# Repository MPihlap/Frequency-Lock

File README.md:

# Frequency-Lock

## Demonstration video:
https://www.youtube.com/watch?v=SHbAAHV13OE

## Overview
Result of a hardware project done for a course at University of Tartu. It is a custom board design built around the STM32F4 microcontroller. 
The system records audio in 0.2 second buffers, performs RFFT and analyzes the output to see if the correct note is being played.

The code is fully compatible with the STM32F4 Discovery board.

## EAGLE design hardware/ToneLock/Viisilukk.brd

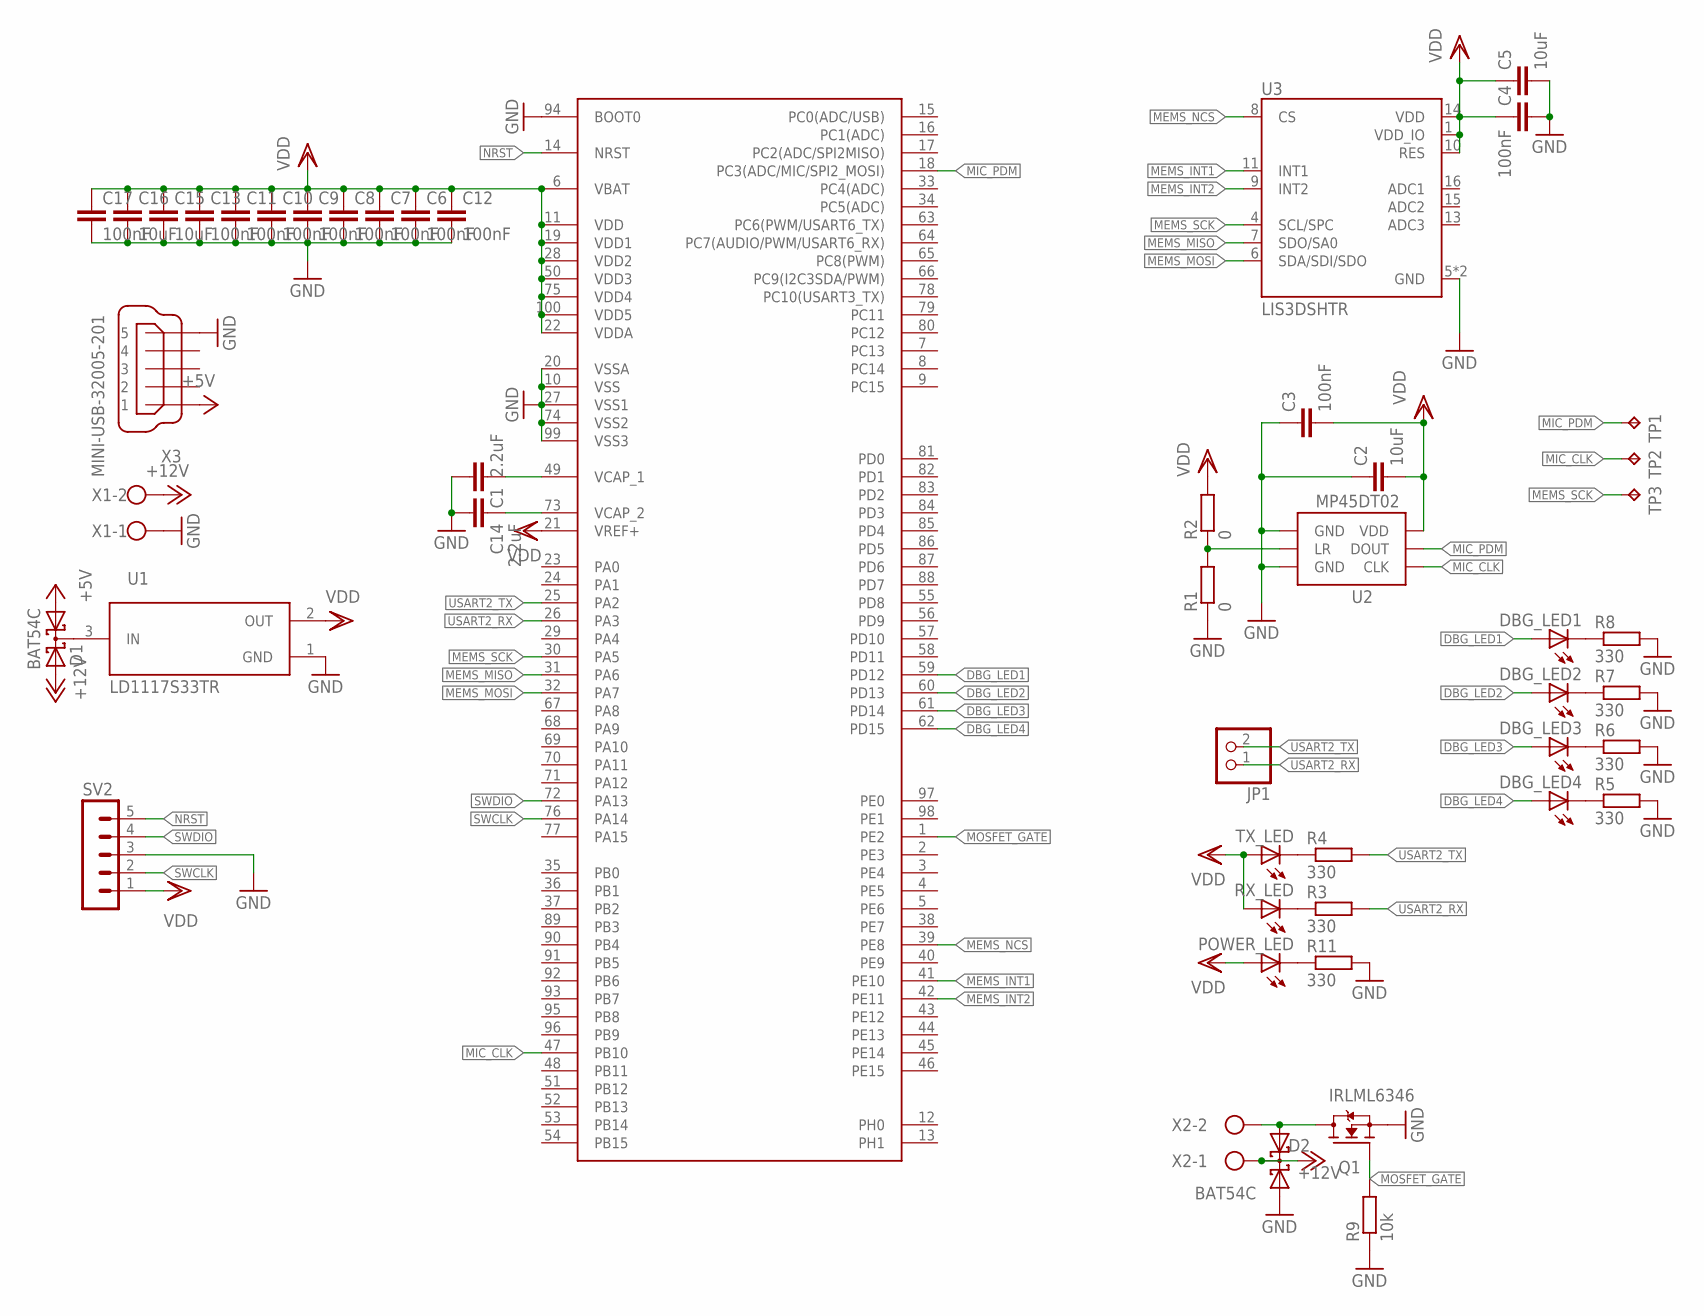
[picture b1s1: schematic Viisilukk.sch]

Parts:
C1, C14: 2.2uF; C0603
C2, C5, C15, C16: 10uF; C0805
C3, C4, C6, C7, C8, C9, C10, C11, C12, C13, C17: 100nF; C0603
D1, D2: BAT54C; SOT23
DBG_LED1, DBG_LED2, DBG_LED3, DBG_LED4: LEDCHIP-LED0603; CHIP-LED0603
JP1: PINHD-1X2; 1X02
POWER_LED: LEDCHIP-LED0603; CHIP-LED0603
Q1: IRLML6346; SOT23
R1, R2: 0; R0603
R3, R4, R5, R6, R7, R8, R11: 330; R0603
R9: 10k; R0603
RX_LED: LEDCHIP-LED0603; CHIP-LED0603
SV2: MA05-1
TP1, TP2, TP3: TPB2,54; B2,54
TX_LED: LEDCHIP-LED0603; CHIP-LED0603
U1: LD1117S33TR; SOT230P700X180-4N
U2: MP45DT02; ST_HLGA6
U3: LIS3DSHTR; LGA16R50P5X3_300X300X100N
U$1: STM32F407STM32D40X; LQFP100
X1, X2: W237-102
X3: MINI-USB-32005-201; 32005-201

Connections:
+5V: D1.1 (A1), X3.1
+12V: D1.2 (A2), D2.3 (CC), X1.2, X2.1
DBG_LED1: DBG_LED1.A, U$1.59 (PD12)
DBG_LED2: DBG_LED2.A, U$1.60 (PD13)
DBG_LED3: DBG_LED3.A, U$1.61 (PD14)
DBG_LED4: DBG_LED4.A, U$1.62 (PD15)
GND: C1.2, C2.1, C3.1, C4.2, C5.2, C6.2, C7.2, C8.2, C9.2, C10.2, C11.2, C12.2, C13.2, C14.2, C15.2, C16.2, C17.2, D2.1 (A1), Q1.2 (S), R1.1, R5.2, R6.2, R7.2, R8.2, R9.1, R11.2, SV2.3, U1.1 (GND), U2.1 (GND), U2.3 (GND), U3.5 (GND), U3.12 (GND), U$1.10 (VSS), U$1.20 (VSSA), U$1.27 (VSS1), U$1.74 (VSS2), U$1.94 (BOOT0), U$1.99 (VSS3), X1.1, X3.5
MEMS_INT1: U3.11 (INT1), U$1.41 (PE10)
MEMS_INT2: U3.9 (INT2), U$1.42 (PE11)
MEMS_MISO: U3.7 (SDO/SA0), U$1.31 (PA6)
MEMS_MOSI: U3.6 (SDA/SDI/SDO), U$1.32 (PA7)
MEMS_NCS: U3.8 (CS), U$1.39 (PE8)
MEMS_SCK: TP3.TP, U3.4 (SCL/SPC), U$1.30 (PA5)
MIC_CLK: TP2.TP, U2.4 (CLK), U$1.47 (PB10)
MIC_PDM: TP1.TP, U2.5 (DOUT), U$1.18 (PC3(ADC/MIC/SPI2_MOSI))
MOSFET_GATE: Q1.1 (G), R9.2, U$1.1 (PE2)
unnamed: POWER_LED.C, R11.1
unnamed: C14.1, U$1.73 (VCAP_2)
unnamed: R1.2, R2.1, U2.2 (LR)
unnamed: R3.1, RX_LED.C
unnamed: C1.1, U$1.49 (VCAP_1)
unnamed: D1.3 (CC), U1.3 (IN)
unnamed: R4.1, TX_LED.C
unnamed: DBG_LED4.C, R5.1
unnamed: DBG_LED3.C, R6.1
unnamed: DBG_LED2.C, R7.1
unnamed: DBG_LED1.C, R8.1
unnamed: D2.2 (A2), Q1.3 (D), X2.2
NRST: SV2.5, U$1.14 (NRST)
SWCLK: SV2.2, U$1.76 (PA14)
SWDIO: SV2.4, U$1.72 (PA13)
USART2_RX: JP1.1, R3.2, U$1.26 (PA3)
USART2_TX: JP1.2, R4.2, U$1.25 (PA2)
VDD: C2.2, C3.2, C4.1, C5.1, C6.1, C7.1, C8.1, C9.1, C10.1, C11.1, C12.1, C13.1, C15.1, C16.1, C17.1, POWER_LED.A, R2.2, RX_LED.A, SV2.1, TX_LED.A, U1.2 (OUT), U2.6 (VDD), U3.1 (VDD_IO), U3.10 (RES), U3.14 (VDD), U$1.6 (VBAT), U$1.11 (VDD), U$1.19 (VDD1), U$1.21 (VREF+), U$1.22 (VDDA), U$1.28 (VDD2), U$1.50 (VDD3), U$1.75 (VDD4), U$1.100 (VDD5)

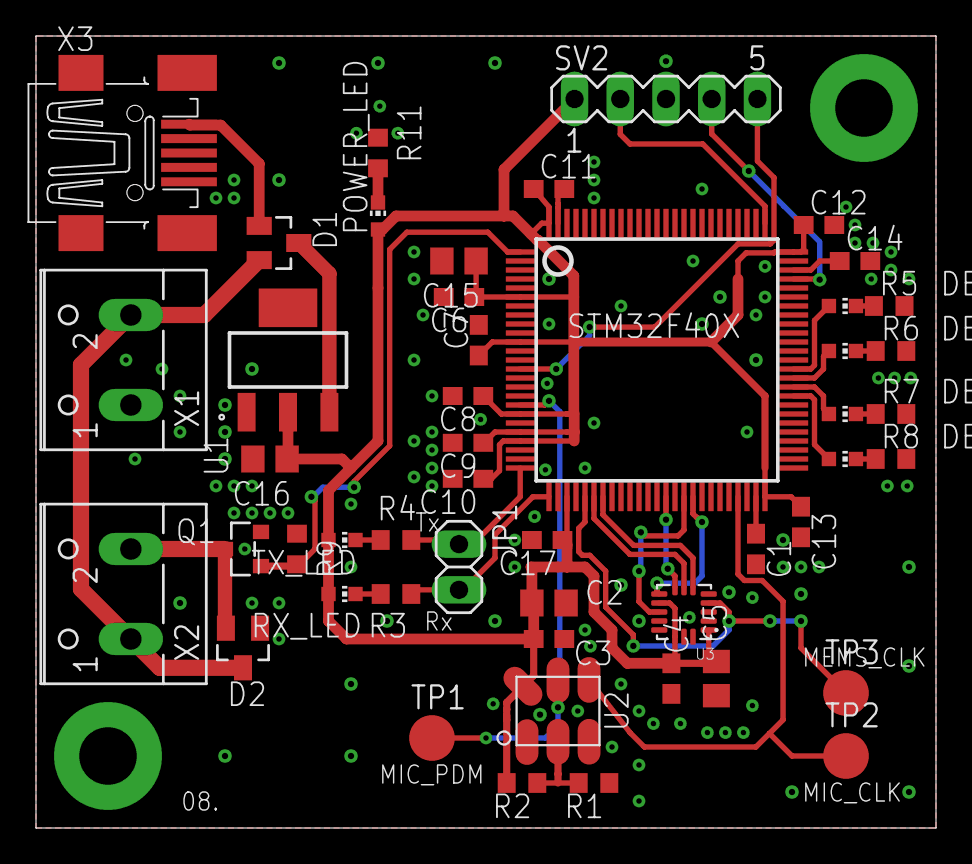
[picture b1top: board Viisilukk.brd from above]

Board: 2 copper layers, 50.0 x 44.0 mm, 49 parts (0 on the bottom side), 34 nets.

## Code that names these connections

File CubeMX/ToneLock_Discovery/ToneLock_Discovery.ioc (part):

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Mcu.Name=STM32F407V(E-G)Tx
Mcu.Package=LQFP100
Mcu.UserName=STM32F407VGTx
PA13.GPIOParameters=GPIO_Label
PA13.GPIO_Label=SWDIO
PA13.Mode=Serial_Wire
PA13.Signal=SYS_JTMS-SWDIO
PA14.GPIOParameters=GPIO_Label
PA14.GPIO_Label=SWCLK
PA14.Mode=Serial_Wire
PA14.Signal=SYS_JTCK-SWCLK
PA2.Mode=Asynchronous
PA2.Signal=USART2_TX
PA3.Mode=Asynchronous
PA3.Signal=USART2_RX
PA4.GPIOParameters=GPIO_Speed,GPIO_PuPd,GPIO_Label,GPIO_Mode
PA4.GPIO_Label=I2S3_WS [CS43L22_LRCK]
PA4.GPIO_Mode=GPIO_MODE_AF_PP
PA4.GPIO_PuPd=GPIO_NOPULL
PA4.GPIO_Speed=GPIO_SPEED_FREQ_LOW
PA4.Signal=I2S3_WS
PA5.GPIOParameters=GPIO_Speed,GPIO_PuPd,GPIO_Label,GPIO_Mode
PA5.GPIO_Label=SPI1_SCK [LIS302DL_SCL/SPC]
PA5.GPIO_Mode=GPIO_MODE_AF_PP
PA5.GPIO_PuPd=GPIO_NOPULL
PA5.GPIO_Speed=GPIO_SPEED_FREQ_LOW
PA5.Mode=Full_Duplex_Master
PA5.Signal=SPI1_SCK
PA6.GPIOParameters=GPIO_Speed,GPIO_PuPd,GPIO_Label,GPIO_Mode
PA6.GPIO_Label=SPI1_MISO [LIS302DL_SDO]
PA6.GPIO_Mode=GPIO_MODE_AF_PP
PA6.GPIO_PuPd=GPIO_NOPULL
PA6.GPIO_Speed=GPIO_SPEED_FREQ_LOW
PA6.Mode=Full_Duplex_Master
PA6.Signal=SPI1_MISO
PA7.GPIOParameters=GPIO_Speed,GPIO_PuPd,GPIO_Label,GPIO_Mode
PA7.GPIO_Label=SPI1_MOSI [LIS302DL_SDA/SDI/SDO]
PA7.GPIO_Mode=GPIO_MODE_AF_PP
PA7.GPIO_PuPd=GPIO_NOPULL
PA7.GPIO_Speed=GPIO_SPEED_FREQ_LOW
PA7.Mode=Full_Duplex_Master
PA7.Signal=SPI1_MOSI
PB10.GPIOParameters=GPIO_Speed,GPIO_PuPd,GPIO_Label,GPIO_Mode
PB10.GPIO_Label=CLK_IN [MP45DT02_CLK]
PB10.GPIO_Mode=GPIO_MODE_AF_PP
PB10.GPIO_PuPd=GPIO_NOPULL
PB10.GPIO_Speed=GPIO_SPEED_FREQ_LOW
PB10.Mode=Half_Duplex_Master
PB10.Signal=I2S2_CK
PB12.Mode=Half_Duplex_Master
PB12.Signal=I2S2_WS
PB2.GPIOParameters=GPIO_PuPd,GPIO_Label,GPIO_Mode
PB2.GPIO_Label=BOOT1
PB2.GPIO_Mode=GPIO_MODE_INPUT
PB2.GPIO_PuPd=GPIO_NOPULL
PB2.Signal=GPIO_Input
PC0.GPIOParameters=GPIO_Speed,PinState,GPIO_PuPd,GPIO_Label
PC0.GPIO_Label=OTG_FS_PowerSwitchOn
PC0.GPIO_PuPd=GPIO_NOPULL
PC0.GPIO_Speed=GPIO_SPEED_FREQ_LOW
PC0.PinState=GPIO_PIN_SET
PC0.Signal=GPIO_Output
PC14-OSC32_IN.GPIOParameters=GPIO_Label
PC14-OSC32_IN.GPIO_Label=PC14-OSC32_IN
PC14-OSC32_IN.Mode=LSE-External-Oscillator
PC14-OSC32_IN.Signal=RCC_OSC32_IN
PC15-OSC32_OUT.GPIOParameters=GPIO_Label
PC15-OSC32_OUT.GPIO_Label=PC15-OSC32_OUT
PC15-OSC32_OUT.Mode=LSE-External-Oscillator
PC15-OSC32_OUT.Signal=RCC_OSC32_OUT
PC3.Mode=Half_Duplex_Master
PC3.Signal=I2S2_SD
PD12.GPIOParameters=GPIO_Speed,GPIO_PuPd,GPIO_Label
PD12.GPIO_Label=LD4 [Green Led]
PD12.GPIO_PuPd=GPIO_NOPULL
PD12.GPIO_Speed=GPIO_SPEED_FREQ_LOW
PD12.Signal=GPIO_Output
PD13.GPIOParameters=GPIO_Speed,GPIO_PuPd,GPIO_Label
PD13.GPIO_Label=LD3 [Orange Led]
PD13.GPIO_PuPd=GPIO_NOPULL
PD13.GPIO_Speed=GPIO_SPEED_FREQ_LOW
PD13.Signal=GPIO_Output
PD14.GPIOParameters=GPIO_Speed,GPIO_PuPd,GPIO_Label
PD14.GPIO_Label=LD5 [Red Led]
PD14.GPIO_PuPd=GPIO_NOPULL
PD14.GPIO_Speed=GPIO_SPEED_FREQ_LOW
PD14.Signal=GPIO_Output
PD15.GPIOParameters=GPIO_Speed,GPIO_PuPd,GPIO_Label
PD15.GPIO_Label=LD6 [Blue Led]
PD15.GPIO_PuPd=GPIO_NOPULL
PD15.GPIO_Speed=GPIO_SPEED_FREQ_LOW
PD15.Signal=GPIO_Output
PE1.GPIOParameters=GPIO_PuPd,GPIO_Label,GPIO_ModeDefaultEXTI
PE1.GPIO_Label=MEMS_INT2 [LIS302DL_INT2]
PE1.GPIO_ModeDefaultEXTI=GPIO_MODE_EVT_RISING
PE1.GPIO_PuPd=GPIO_NOPULL
PE1.Signal=GPXTI1
PE2.Signal=GPIO_Output
PE3.GPIOParameters=GPIO_Speed,GPIO_PuPd,GPIO_Label
PE3.GPIO_Label=CS_I2C/SPI [LIS302DL_CS_I2C/SPI]
PE3.GPIO_PuPd=GPIO_NOPULL
PE3.GPIO_Speed=GPIO_SPEED_FREQ_LOW
PE3.Signal=GPIO_Output
PH0-OSC_IN.GPIOParameters=GPIO_Label
PH0-OSC_IN.GPIO_Label=PH0-OSC_IN
PH0-OSC_IN.Mode=HSE-External-Oscillator
PH0-OSC_IN.Signal=RCC_OSC_IN
PH1-OSC_OUT.GPIOParameters=GPIO_Label
PH1-OSC_OUT.GPIO_Label=PH1-OSC_OUT
PH1-OSC_OUT.Mode=HSE-External-Oscillator
PH1-OSC_OUT.Signal=RCC_OSC_OUT
RCC.HSE_VALUE=8000000
RCC.SYSCLKFreq_VALUE=168000000
RCC.SYSCLKSource=RCC_SYSCLKSOURCE_PLLCLK
board=STM32F4DISCOVERY
boardIOC=true

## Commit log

2018-09-15 Initial commit, implemented lock in python
2018-09-21 Inital project setup
2018-09-24 Added src
2018-09-24 UART test, not working yet
2018-09-25 Added .gitignore
2018-10-01 Refactored firmware into separate folder, added picture of devboard pinout
2018-10-01 Refactor
2018-10-01 Added schematic for discovery board
2018-10-08 Added Eagle project for hardware
2018-10-08 Added libraries folder to hardware
2018-10-08 Added accelerometer, microphone into schematic and added libraries
2018-10-08 Renamed datasheets and Added UART pins
2018-10-08 Minor touches
2018-10-08 Changed UART to use USART2
2018-10-08 Working USART2
2018-10-08 Added audio docs
2018-10-09 Synced board
2018-10-09 Changed VCC header
2018-10-16 Added BOOT0 and NRST setups, power LED, Debugger
2018-10-23 Completed schematic
2018-11-06 Fixed MOSFET switch, grouped all components
2018-11-12 All VCC and signals routed, GND TODO
2018-11-12 Added final signal route
2018-11-13 Schematic ready for pour, rewired all supply lines
2018-11-20 Routed, polygon poured, ready in theory
2018-11-20 Board now 50x44
2018-11-27 Ready for polygon
2018-11-27 Hardware ready to generate gerber
2018-11-27 Renamed to Viisilukk, final design
2018-12-21 Implemented pdm filter and reworked main
2019-01-09 Got data from mic
2019-01-15 Working(?) blocking audio receive
2019-01-15 Untested implementation of continuous I2S reception
2019-01-16 Tried new approach to recursive interrupts, didn't work
2019-01-17 Not working closer to hardware solution
2019-01-17 This should work in theory, currently overrun bug
2019-01-18 Successful reception of garbage audio
2019-01-18 Added DSP
2019-01-20 Commit before generating code
2019-01-20 It compiled
2019-01-20 No longer hardfaults
2019-01-21 Reformatted
2019-01-21 Actual audio-like signal
2019-01-22 Working audio recording, non hardfault fft
2019-01-24 Working cycle of reading and processing a single PCM buffer
2019-01-24 Working waiting for one note
2019-01-24 Working lock based on the lick
2019-01-24 Added comments
2019-01-25 Added led blinking to signal progression, fixed timer
2019-01-25 Added error measurements in cents
2019-01-25 Fixed float division bug
2019-01-25 Fixed notes in my heart will go on
2019-03-09 Refactored project structure and removed broken code
2019-03-15 Fixed names of src and inc folders
